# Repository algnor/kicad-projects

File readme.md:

repository for private/school related KiCad projects

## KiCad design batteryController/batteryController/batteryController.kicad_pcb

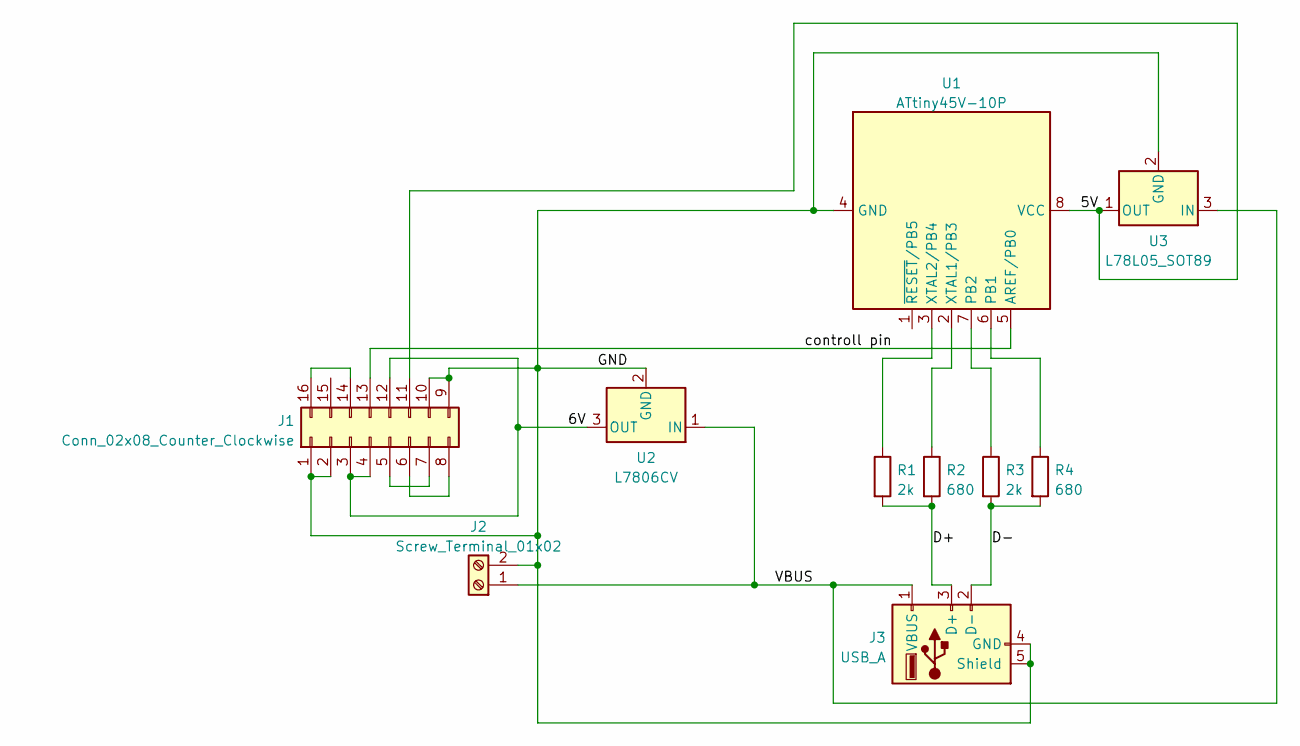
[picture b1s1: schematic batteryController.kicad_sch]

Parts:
J1: Conn_02x08_Counter_Clockwise; PinHeader_2x08_P2.54mm_Vertical
J2: Screw_Terminal_01x02; TerminalBlock_bornier-2_P5.08mm
J3: USB_A; USB_A_CNCTech_1001-011-01101_Horizontal
R1, R3: 2k; R_0603_1608Metric
R2, R4: 680; R_0603_1608Metric
U1: ATtiny45V-10P; DIP-8_W7.62mm_Socket
U2: L7806CV; TO-220-3_Horizontal_TabDown
U3: L78L05_SOT89; SOT-89-3

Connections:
/5V: J1.11, U1.8 (VCC), U3.1 (OUT)
/6V: J1.3, J1.4, J1.12, U2.3 (OUT)
/D+: J3.3 (D+), R1.2, R2.2
/D-: J3.2 (D-), R3.2, R4.2
/GND: J1.1, J1.2, J1.9, J1.10, J2.2, J3.4 (GND), J3.5 (Shield), U1.4 (GND), U2.2 (GND), U3.2 (GND)
/VBUS: J2.1, J3.1 (VBUS), U2.1 (IN), U3.3 (IN)
/controll pin: J1.13, U1.5 (AREF/PB0)
unnamed: J1.5, J1.7
unnamed: J1.6, J1.8
unnamed: J1.14, J1.16
unnamed: R1.1, U1.3 (XTAL2/PB4)
unnamed: R2.1, U1.2 (XTAL1/PB3)
unnamed: R3.1, U1.7 (PB2)
unnamed: R4.1, U1.6 (PB1)

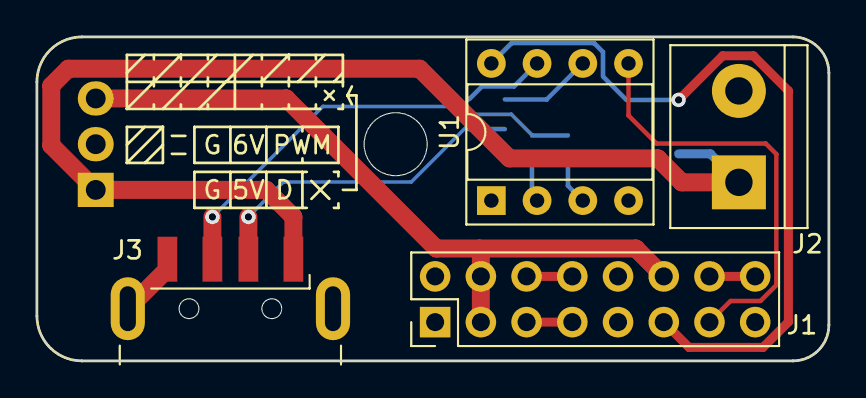
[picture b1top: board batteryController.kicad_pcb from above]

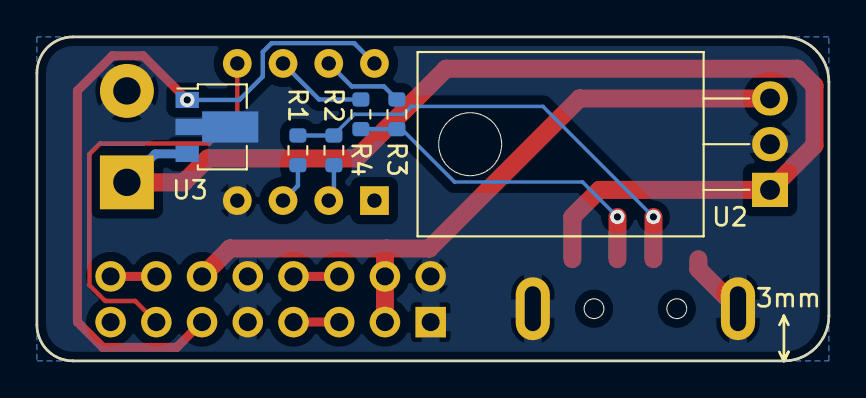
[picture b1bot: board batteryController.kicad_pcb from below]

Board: 2 copper layers, 44.0 x 18.0 mm, 10 parts (6 on the bottom side), 14 nets.

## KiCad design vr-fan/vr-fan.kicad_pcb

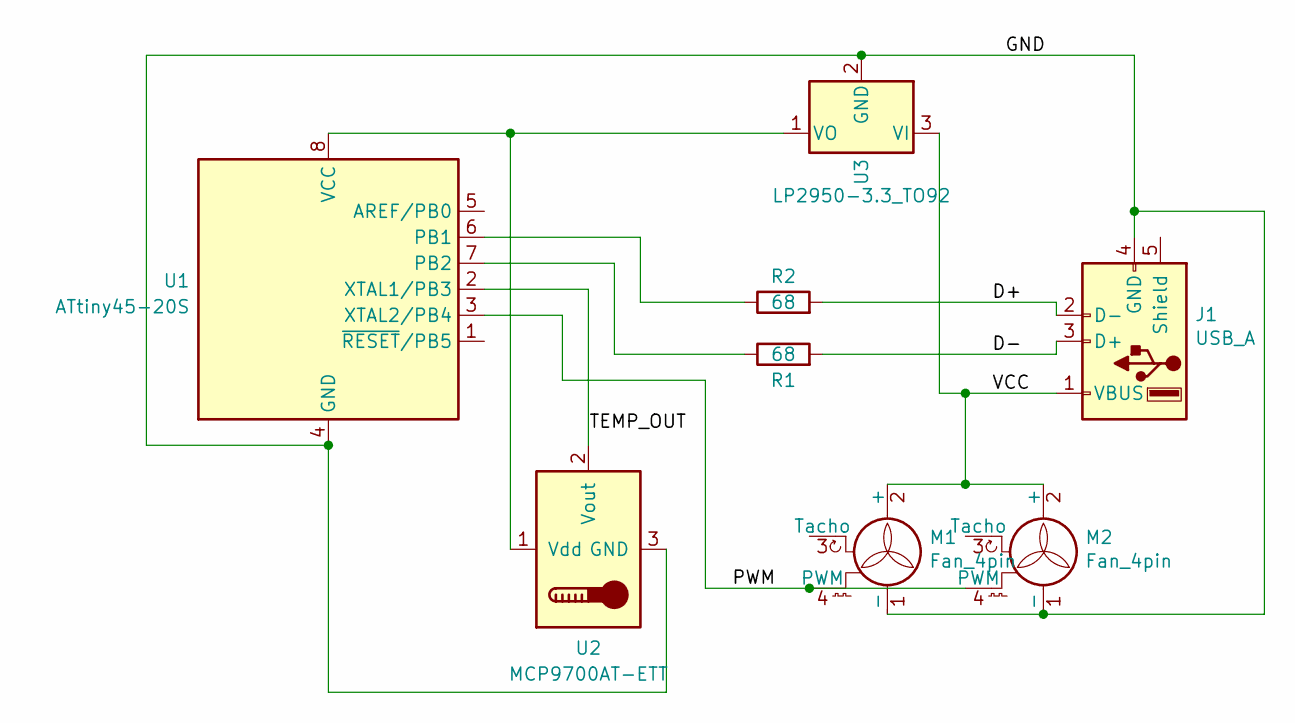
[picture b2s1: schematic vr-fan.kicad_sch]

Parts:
J1: USB_A; USB_A_CNCTech_1001-011-01101_Horizontal
M1, M2: Fan_4pin; FanPinHeader_1x04_P2.54mm_Vertical
R1, R2: 68; R_1206_3216Metric
U1: ATtiny45-20S; SOIC-8W_5.3x5.3mm_P1.27mm
U2: MCP9700AT-ETT; SOT-23
U3: LP2950-3.3_TO92; SOT-23

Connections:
/D+: J1.2 (D-), R2.2
/D-: J1.3 (D+), R1.2
/GND: J1.4 (GND), J1.5 (Shield), M1.1 (-), M2.1 (-), U1.4 (GND), U2.3 (GND), U3.2 (GND)
/PWM: M1.4 (PWM), M2.4 (PWM), U1.3 (XTAL2/PB4)
/TEMP_OUT: U1.2 (XTAL1/PB3), U2.2 (Vout)
/VCC: J1.1 (VBUS), M1.2 (+), M2.2 (+), U3.3 (VI)
unnamed: R1.1, U1.7 (PB2)
unnamed: R2.1, U1.6 (PB1)
unnamed: U1.8 (VCC), U2.1 (Vdd), U3.1 (VO)

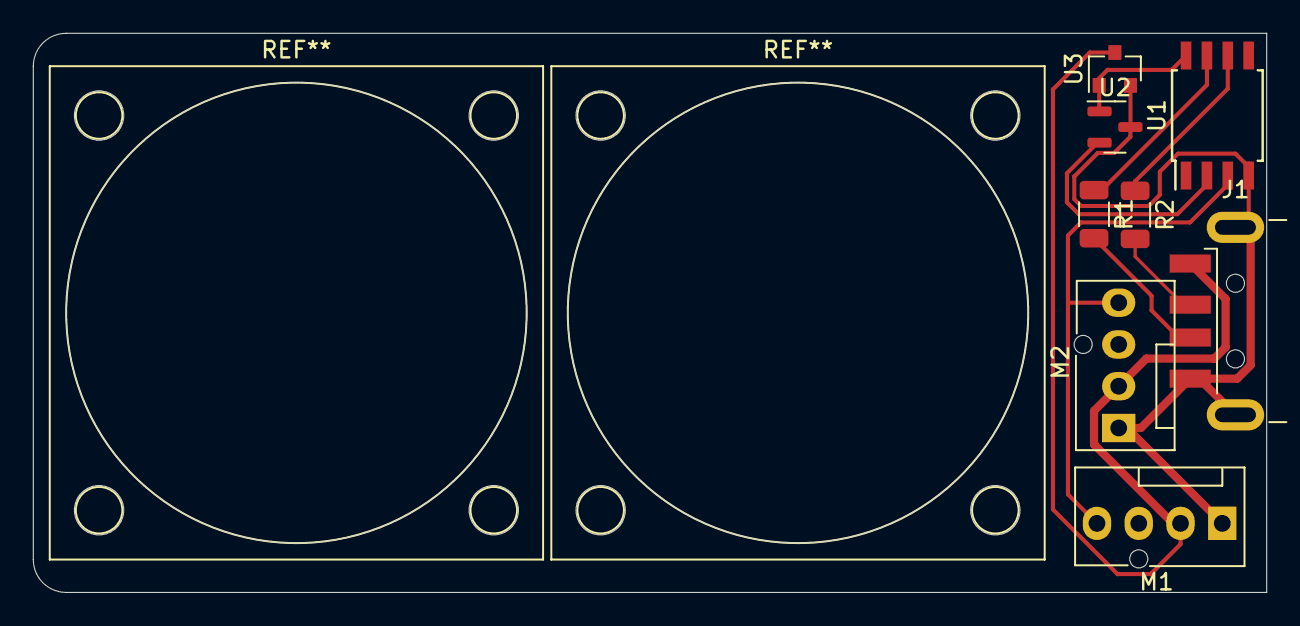
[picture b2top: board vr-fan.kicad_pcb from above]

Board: 2 copper layers, 75.0 x 34.0 mm, 8 parts (0 on the bottom side), 9 nets.

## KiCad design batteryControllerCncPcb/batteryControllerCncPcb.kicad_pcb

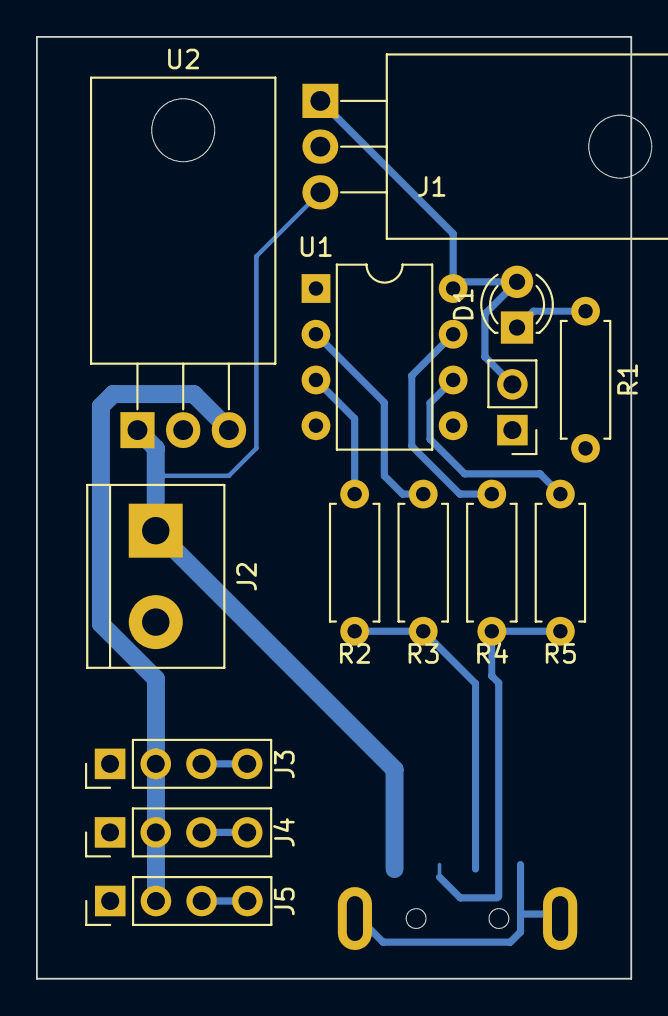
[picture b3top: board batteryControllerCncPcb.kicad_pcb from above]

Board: 2 copper layers, 33.0 x 52.3 mm, 15 parts (1 on the bottom side), 14 nets.

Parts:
D1: LED; LED_D3.0mm
J1: Conn_01x02_Male; PinHeader_1x02_P2.54mm_Vertical
J2: Screw_Terminal_01x02; TerminalBlock_bornier-2_P5.08mm
J3, J4, J5: Conn_01x04_Male; PinHeader_1x04_P2.54mm_Vertical
J6: USB_A; USB_A_CNCTech_1001-011-01101_Horizontal
R1: 220; R_Axial_DIN0207_L6.3mm_D2.5mm_P7.62mm_Horizontal
R2, R3, R4, R5: R; R_Axial_DIN0207_L6.3mm_D2.5mm_P7.62mm_Horizontal
U1: ATtiny13V-10P; DIP-8_W7.62mm
U2: L7806CV; TO-220-3_Horizontal_TabDown
U3: L78L05_TO92; TO-220-3_Horizontal_TabDown

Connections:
/5V: D1.2 (A), J1.2, U1.8 (VCC), U3.1 (VO)
/6V: J3.2, J4.2, J5.2, U2.3 (OUT)
/GND: J1.1, J2.2, J3.1, J4.1, J5.1, J6.4 (GND), J6.5 (Shield), R1.2, U1.4 (GND), U2.2 (GND), U3.2 (GND)
/VBUS: J2.1, J6.1 (VBUS), U2.1 (IN), U3.3 (VI)
unnamed: D1.1 (K), R1.1
unnamed: J3.3, J3.4
unnamed: J4.3, J4.4
unnamed: J5.3, J5.4
unnamed: J6.2 (D-), R4.2, R5.2
unnamed: J6.3 (D+), R2.2, R3.2
unnamed: R2.1, U1.3 (PB4)
unnamed: R3.1, U1.2 (PB3)
unnamed: R4.1, U1.7 (PB2)
unnamed: R5.1, U1.6 (PB1)

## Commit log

2022-03-11 created repository
2022-03-11 merged laptop and desktop
2022-03-11 removed school folder and moved files to root folder
2022-03-11 removed test/
2022-03-11 removed unnecesary folder depth in qc3-trigger
2022-03-11 remade basically the entire thing
2022-03-11 fixed DRC warnings
2022-03-11 added radius marker
2022-03-13 remade it again...
2022-03-13 moved battery controller to its own repository
